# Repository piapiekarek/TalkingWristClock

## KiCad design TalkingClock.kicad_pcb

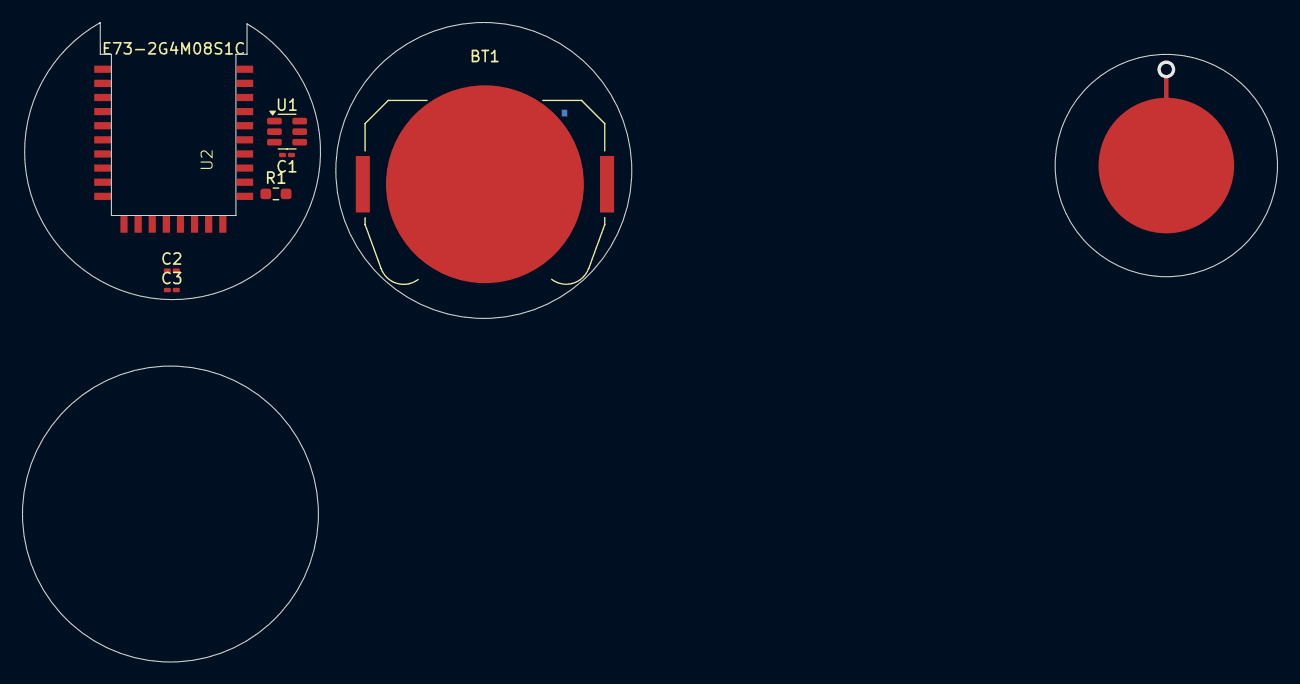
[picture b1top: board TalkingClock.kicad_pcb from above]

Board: 2 copper layers, 112.9 x 57.5 mm, 8 parts (1 on the bottom side), 7 nets.

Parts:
BT1: Battery_Cell; BatteryHolder_Keystone_3034_1x20mm
C1, C2: 100n; C_0201_0603Metric_Pad0.64x0.40mm_HandSolder
C3: C_Small; C_0201_0603Metric_Pad0.64x0.40mm_HandSolder
JP2: SolderJumper_3_Bridged12; SolderJumper-3_P1.3mm_Bridged12_RoundedPad1.0x1.5mm
R1: R; R_0603_1608Metric_Pad0.98x0.95mm_HandSolder
U1: AT42QT1010-TSHR; SOT-23-6
U2: E73-2G4M08S1C; E73-2G4M08S1C-52840 - reverse

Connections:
+BATT: BT1.1 (+), JP2.3 (B)
GND: BT1.2 (-), C1.2, C3.2, JP2.1 (A), U1.2 (VSS)
unnamed: C3.1, R1.2
unnamed: JP2.2 (C), U1.6 (SYNC)
unnamed: C2.2, U1.4 (SNS)
unnamed: C2.1, R1.1, U1.3 (SNSK)
unnamed: C1.1, U1.5 (VDD)

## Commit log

2024-11-14 add Microcontroller
2024-12-19 add things
